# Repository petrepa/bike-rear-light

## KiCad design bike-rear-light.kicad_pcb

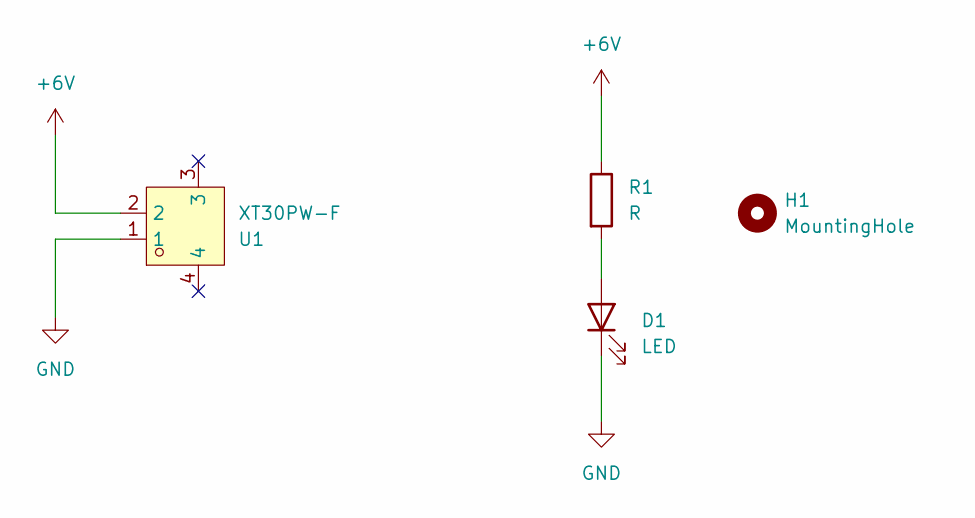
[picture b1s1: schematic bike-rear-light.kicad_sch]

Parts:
D1: LED; LED_0805_2012Metric
H1: MountingHole; MountingHole_5.3mm_M5
R1: R; R_0805_2012Metric
U1: XT30PW-F; CONN-TH_XT30PW-F-1; LCSC Part C2913282

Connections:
+6V: R1.1, U1.2
GND: D1.1 (K), U1.1
unnamed: D1.2 (A), R1.2

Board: 2 copper layers, 4 parts (0 on the bottom side), 3 nets, no tracks yet.

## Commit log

2024-12-10 Added render workflow
2024-12-10 Added kibot yaml
2024-12-10 Modified path of actions workflow
2024-12-14 Added assets folder
2024-12-14 Moved power port
2024-12-14 Update renders
